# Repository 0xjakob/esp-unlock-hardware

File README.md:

# ESP-Unlock PCB

This is the hardware for the [ESP-Unlock software](https://github.com/0xjakob/esp-unlock). Note that the KiCad project has been renamed from `esp_key` to `ESP-Unlock`.

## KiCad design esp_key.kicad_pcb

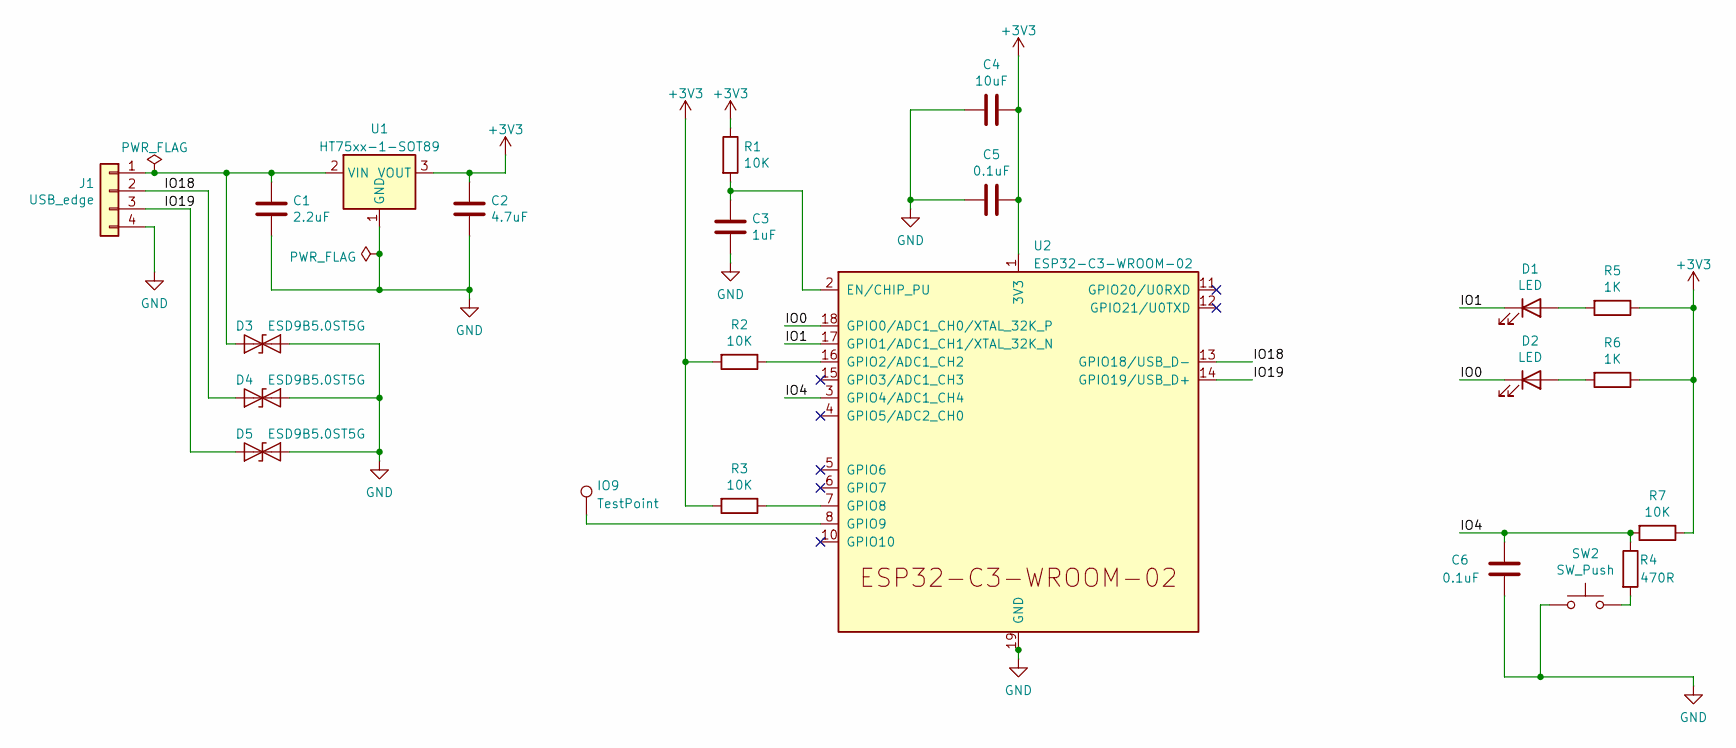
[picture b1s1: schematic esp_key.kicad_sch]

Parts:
C1: 2.2uF; C_0805_2012Metric_Pad1.15x1.40mm_HandSolder
C2: 4.7uF; C_0805_2012Metric_Pad1.15x1.40mm_HandSolder
C3: 1uF; C_0603_1608Metric_Pad1.05x0.95mm_HandSolder
C4: 10uF; C_0805_2012Metric_Pad1.15x1.40mm_HandSolder
C5, C6: 0.1uF; C_0402_1005Metric
D1, D2: LED; LED_0805_2012Metric_Pad1.15x1.40mm_HandSolder
D3, D4, D5: ESD9B5.0ST5G; D_SOD-923
IO9: TestPoint; TestPoint_Loop_D1.80mm_Drill1.0mm_Beaded
J1: USB_edge; USB_A_CNCTech_1001-011-01101_Horizontal
R1, R2, R3, R7: 10K; R_0402_1005Metric
R4: 470R; R_0402_1005Metric
R5, R6: 1K; R_0402_1005Metric
SW2: SW_Push; SW_PUSH_6mm
U1: HT75xx-1-SOT89; SOT-89-3
U2: ESP32-C3-WROOM-02; ESP32-C3-WROOM-02U

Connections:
+3V3: C2.1, C4.1, C5.1, R1.1, R2.2, R3.2, R5.1, R6.1, R7.1, U1.3 (VOUT), U2.1 (3V3)
/IO0: D2.1 (K), U2.18 (GPIO0/ADC1_CH0/XTAL_32K_P)
/IO1: D1.1 (K), U2.17 (GPIO1/ADC1_CH1/XTAL_32K_N)
/IO4: C6.1, R4.1, R7.2, U2.3 (GPIO4/ADC1_CH4)
/IO18: D4.1 (A1), J1.2, U2.13 (GPIO18/USB_D-)
/IO19: D5.1 (A1), J1.3, U2.14 (GPIO19/USB_D+)
GND: C1.2, C2.2, C3.2, C4.2, C5.2, C6.2, D3.2 (A2), D4.2 (A2), D5.2 (A2), J1.4, SW2.1, U1.1 (GND), U2.9 (GND), U2.19 (GND)
unnamed: C1.1, D3.1 (A1), J1.1, U1.2 (VIN)
unnamed: C3.1, R1.2, U2.2 (EN/CHIP_PU)
unnamed: D1.2 (A), R5.2
unnamed: D2.2 (A), R6.2
unnamed: IO9.1, U2.8 (GPIO9)
unnamed: R2.1, U2.16 (GPIO2/ADC1_CH2)
unnamed: R3.1, U2.7 (GPIO8)
unnamed: R4.2, SW2.2

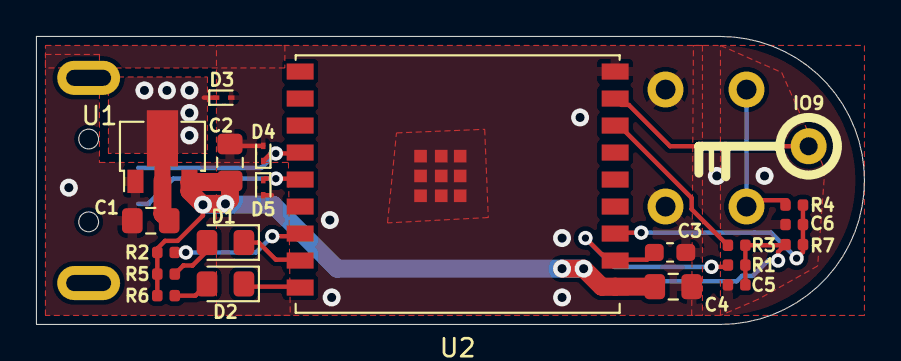
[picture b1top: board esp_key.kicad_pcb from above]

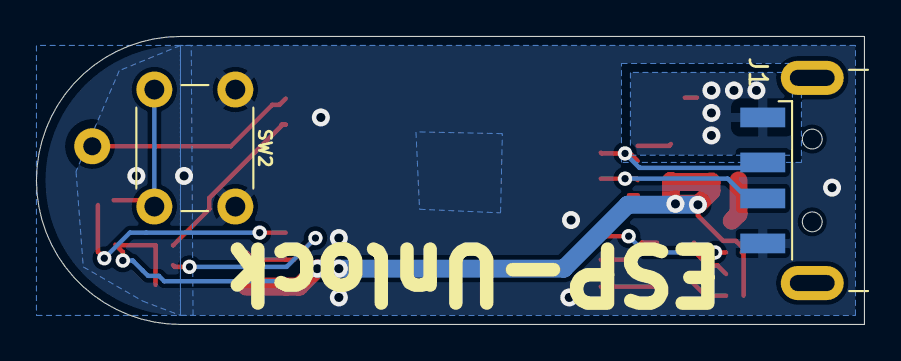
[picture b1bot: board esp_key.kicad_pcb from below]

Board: 2 copper layers, 46.0 x 16.0 mm, 23 parts (2 on the bottom side), 15 nets.
